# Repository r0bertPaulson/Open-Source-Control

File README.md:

# Open-Source-Control
Collection of Open Source IoT Designs

-Unitary Controller Version 3.0 - This device will be suitable for control of automated and networked building equipment at the unitary level. For example, you could control a single airconditioner unit with this device.

Project Status:
1.	Use Version 3.0 - Full BOM and Academic Free License statement to be posted here shortly.

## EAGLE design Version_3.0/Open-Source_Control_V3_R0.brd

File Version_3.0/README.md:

New Modular Board which allows the creation of a family of devices to cover most Building Automation control use cases. 

This board will have headers that can connect to an add-on sub-board and other devices that are application specific.

For example, by adding an airflow sensor and two analog actuator outputs, you will have a device that can control a VAV (Variable Air Volume) terminal unit specifically.

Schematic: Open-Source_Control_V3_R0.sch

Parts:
C1, C2: DNI; C0603
C3, C6, C9, C10, C14, C15, C22, C79, C104, C301, C801, C802, C901: 0.1uF, 6.3V; C0402
C4: 47uF; C0805
C8: 1nF; C0402
C11: 220uF, 6.3V, T491C227K006AT; C/6032-28R
C21: 10uF, 10V; C0805
C85, C87, C88: 2200pF, 6.3V; C0402
C100: 1000uF, 50V, UHE1H102MHD6; PCAP_16X25-THRU-ELECT
C101, C102, C105: 0.47uF, 100V, X7R; 1206
C106: 0.1uF, 50V; 1206
C111, C121, C131, C141, C151, C161: 1uF; C0805
C401, C402, C403: 0.1uF, 16V; C0402
C404, C405: 10uF, 16V; C0805
C406: 4.7uF, 16V, T491A475K016AT; A/3216-18R
C803: 4.7uF, 6.3V; C0402
D1, D4, D5, D6, D7, D19, D31, D32, D33, D34, D302, D402, D802: LTST-C191KGKT; EIA-STD
D3: S1D; SMA
D18: B550C-13-F; SMC
D301, D401, D801: LTST-C191KRKT; EIA-STD
D305, D405: SM712; SOT23-3
D403, D404: MBR0520LT; SOD123
D805: CDSOT23-T24CAN; SOT23-3
EC30, EC31, EC34: 0.1uF, 6.3V; C0402
EC32: 10uF, 10V; C0805
EC33: 1uF, 10V; C0402
EC35: 470pF, 6.3V; C0402
EC36, EC37, EC38, EC39: 15pF, DNI; C0402
EC40: 0.022uF, 10V; C0402
EC41, EC42: 30pF, 50V; C0402
ER98, ER99, ER100, ER105: 1.5K, 1%; R0402
ER101, ER102, ER103, ER104, ER120, ER129: 10K, 1%; R0402
ER106, ER107, ER108, ER109: 49.9, 1%; R0402
ER110, ER111, ER112, ER113, ER114, ER116, ER118, ER119, ER123, ER124: 100, 1%; R0402
ER115, ER117: 470, 1%; R0402
ER122, ER126: 0, 1%; R0402
ER125: 1M, 1%, DNI; R0402
ER127: 10, 1%; R0402
ER128: 12.1K, 1%; R0402
F1: 60V, 750mA, R075; PTH
F401, F402: TBU-CA085-300-WH; TBU-CA
FB7: 150ohm, 800mA; C0805
FUD1, FUD2, FUD3, FUD4, FUD5, FUD6: FIDUCIAL; FIDUCIAL_40MIL
G1: CR2032V
GDT1: 2036-07-B3; 2036-XX-B3
IC2: ULN2003AD; SO16
IC4, IC5: 74HC165D; SO16
IC10, IC11, IC12, IC14: MCP6002SMT; SOIC8
J1, J3, J7, J11, J12, J13, J21, J22, J23, J31, J32, J33, J41, J42, J43, J45, J51, J52, J53, J61, J62, J63, J450, J454: 826646-2; H2-2.54
J24: 6p-2.54; H3-2.54
K1, K2, K3, K4: G5LE-14-CF DC24; JS-M
L2: SRP1265A-470M; SRP1265
MTG1, MTG2, MTG3, MTG4: MOUNT-PAD-ROUND3.6; 3,6-PAD
Q1: MMBT2907; SOT23-BEC
R3, R4, R25, R28, R29, R30, R33: 0, 1%; R0402
R5, R11: 0; R0402
R6, R163: 100K, DNI; R0402
R8, R301, R302, R401, R402, R801, R802: 1K; R0402
R10: 0, 1%; R0805
R12, R13, R26, R164: 1.5K, 1%; R0402
R15: 40.2K; R0402
R18, R22, R39, R40, R41: 4.75K, 1%; R0402
R20, R168, R171, R172, R173, R174: 10K; R0402
R21: 499; R0402
R27, R53, R55, R56, R57, R58, R59, R60, R61, R62, R63, R67, R68, R71, R81, R82, R83: 100K, 1%; R0402
R31: 22, 1%; R0402
R34: .1, 0805; R0805
R35: 1K; RN0804
R54, R64, R65, R66, R70, R72, R73, R74, R75, R76, R77, R78, R79, R80, R84, R85: 100K, 1%, DNI; R0402
R69: 100, 1%; R0402
R86, R87, R88, R89, R90, R91, R92, R169, R170: 10K, 1%; R0402
R181, R182, R183, R184, R185, R186: B72520T0300K062; CT/CN1206
R211, R221, R231, R241, R251, R261: 80, 0.1%; 0309/12
R212, R214, R222, R224, R232, R234, R242, R244, R252, R254, R262, R264: 10K, 1%; R0805
R213, R223, R233, R243, R253, R263: 2K, 1%; R0805
R215, R225, R235, R245, R255, R265: 100K; R0805
R281, R282, R291: 10K; RN0804
R303, R304: 1K, DNI; R0402
R305: 150, 1%; R0805
R901, R902: 1.5K, 1% DNI; R0402
RTC1: DS3231MZ+; SO08
S1, S2: KMR231GLFS; SW4SMD_63X161LS
S11, S12: P101
S13: DS04; DS-04
T4: DA2304-AL; DA230X-AL
TP1, TP2, TP3, TP4, TP11, TP12, TP13, TP14, TP15, TP16, TP21, TP22, TP23, TP24, TP26, TP31, TP32, TP33: TPB0,65; TP_B0,65
TP5, TP6, TP7, TP8, TP9, TP10, TP17, TP18, TP19, TP20: TESTPAD/W_HOLE_1X1
U1: OSD3358-512M-ICB; OSD335X-BGA-400
U2: TPD4S012_DRY_6_P1_M; DRY6
U4: APX811-31UGSOT; SOT143-R
U5: TLVH431; SOT23-3
U6: SN74LVC2G241_DCU_8; DCU8
U16: AT97SC3205T-G3M4400B; QFN32-0.4-4X4MM
U27: LAN8710; LAN8710A-QFN32
U28: TCAN1051HV; BEAGLEBONE_BLUE_D8
U29: MAX3483EESA+T; 21-0041B_8
U40: ISO3086TDW; DW16
VREG1: LM2596S-5.0; TO263-5
VREG2: L7824CV; 78XXL
VREG4: TPS76350; DBV5
X1: 10118194-0001LF; 10118194-0001LF(MICRO-USB-B-AMPHENOL-FCI)
X2: J0011D01BNL
X3, X10, X11, X12, X31: MC4
X4: CTI-JTAG
X5: DM3CS-SF
X6: 6p-2.54; H6-2.54
X7, X8: TH-2X10; H2X10-2.54
X9: 5600200420
X21: MC12
X24: MSTBA2
X41: MSTBA3
Y7: ECS-250-12-30-GN-TR; XTAL_2-SMD(5X3.2MM)

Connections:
1P8V_REF_1: IC10.8 (V+), IC11.8 (V+), IC14.1 (OUT), IC14.2 (-IN), R212.2, R222.2, R232.2, R242.2
1P8V_REF_2: IC12.8 (V+), IC14.6 (-IN), IC14.7 (OUT), R252.2, R262.2
5V_OUT: D18.C, L2.1, VREG1.2 (OUT)
24LIN_IN: C105.1, J24.1, VREG2.IN
24VAC: D3.A, F1.P$2 (2)
24VAC_IN: F1.P$1 (1), X3.4, X24.1
24VDC_AUX: C106.1, D19.1 (A), D31.1 (A), D32.1 (A), D33.1 (A), D34.1 (A), IC2.9 (CD+), J24.3, K1.1, K2.1, K3.1, K4.1, VREG2.OUT, X8.11, X8.19, X31.4
24VDC_UNREG: C100.1, C101.1, D3.C, J24.2, VREG1.1 (IN)
41_A: F402.1, GDT1.1, X41.2
41_B: F401.1, GDT1.2, X41.1
485_A: D305.1, R304.2, R305.2, U29.6 (A), X3.2
485_B: D305.2, R303.1, R305.1, U29.7 (B), X3.3
485_RXD: D402.2 (C), J45.1, U40.5 (R)
485_TXD: D401.2 (C), J45.2, U40.8 (D)
AGND: C8.2, C9.2, C10.2, C111.2, C121.2, C131.2, C141.2, C151.2, C161.2, IC10.4 (V-), IC11.4 (V-), IC12.4 (V-), J7.1, R25.2, R181.2, R182.2, R183.2, R184.2, R185.2, R186.2, R211.1, R213.2, R215.2, R221.1, R223.2, R225.2, R231.1, R233.2, R235.2, R241.1, R243.2, R245.2, R251.1, R253.2, R255.2, R261.1, R263.2, R265.2, U1.Y9 (AGND_ADC), X10.2, X10.4, X11.2, X11.4, X12.2, X12.4
AIN0: U1.Y10 (AIN0)
AIN1: IC10.1 (OUT), IC10.2 (-IN), R215.1, U1.W10 (AIN1)
AIN2: IC10.6 (-IN), IC10.7 (OUT), R225.1, U1.V10 (AIN2)
AIN3: IC11.1 (OUT), IC11.2 (-IN), R235.1, U1.V9 (AIN3)
AIN4: IC11.6 (-IN), IC11.7 (OUT), R245.1, U1.Y11 (AIN4)
AIN5: IC12.1 (OUT), IC12.2 (-IN), R255.1, U1.W11 (AIN5)
AIN6: IC12.6 (-IN), IC12.7 (OUT), R265.1, U1.V11 (AIN6)
AIN7: U1.U12 (PMIC_MUX_OUT), U1.V12 (AIN7)
B03_NO: K3.NO (S), X21.6
BAT_SENSE: TP6.P$1, U1.E19 (PMIC_BAT_SENSE)
BO1: K1.2, R171.2, X8.10
BO1_AUTO: IC2.16 (O1), X8.9
BO1_C: K1.C, X21.11
BO1_NC: K1.NC (O), X21.10
BO1_NO: K1.NO (S), X21.12
BO2: K2.2, R172.2, X8.8
BO2_AUTO: IC2.15 (O2), X8.7
BO2_C: K2.C, X21.8
BO2_NC: K2.NC (O), X21.7
BO2_NO: K2.NO (S), X21.9
BO3: K3.2, R173.2, X8.6
BO3_AUTO: IC2.14 (O3), X8.5
BO3_C: K3.C, X21.5
BO3_NC: K3.NC (O), X21.4
BO4: K4.2, R174.2, X8.4
BO4_AUTO: IC2.13 (O4), X8.3
BO4_C: K4.C, X21.2
BO4_NC: K4.NC (O), X21.1
BO4_NO: K4.NO (S), X21.3
BO5_AUTO: IC2.12 (O5), X8.1
BO6_AUTO: IC2.11 (O6), X8.12
B_UART0_RX: R27.2, U6.2 (1A), X6.4
B_UART0_TX: U6.3 (2Y), X6.5
CAN1_RXD: D802.2 (C), U1.W7 (UART1_TXD), U28.4 (RXD)
CAN1_TXD: D801.2 (C), U1.Y7 (UART1_RXD), U28.1 (TXD)
CAN_H: D805.2, U28.7 (CANH), X31.3
CAN_L: D805.1, U28.6 (CANL), X31.2
CGND: MTG1.B3,6, MTG2.B3,6, MTG3.B3,6, MTG4.B3,6, R34.2, X1.CGND1 (SGND1), X1.CGND2 (SGND2), X1.CGND3 (SGND3), X1.CGND4 (SGND4), X1.CGND5 (SGND5), X1.CGND6 (SGND6), X2.S1 (SHD1), X2.S2 (SHD2), X5.9 (GND_1), X5.10 (GND_2), X5.11 (GND_3), X5.13 (GND_4)
CLKOUT2: C2.2, R3.2, X4.18 (EMU3)
CRS: ER124.1, U27.14 (CRS)
EEPROM_WP: J1.1, U1.M2 (EEPROM_WP)
EHRPWM1A: U1.C13 (GPMC_A2), X8.15
EHRPWM1B: U1.A12 (GPMC_A3)
EHRPWM2A: U1.A17 (GPMC_AD8), X8.13
EHRPWM2B: U1.C16 (GPMC_AD9), X8.14
E_LED_GRN: U27.3 (LED1/REGOFF), X2.9 (GRNA)
E_LED_YEL: ER120.2, U27.2 (LED2/!INTSEL), X2.12 (YELA)
GND: C1.1, C2.1, C3.2, C4.2, C6.1, C11.-, C14.2, C15.2, C21.2, C22.2, C79.2, C85.2, C87.2, C88.2, C100.2, C101.2, C102.2, C104.2, C105.2, C106.2, C301.2, C401.2, C404.2, C801.2, C802.2, C803.2, C901.2, D18.A, D305.3, D805.3, EC30.2, EC31.2, EC32.2, EC33.2, EC34.2, EC35.2, EC36.2, EC37.2, EC38.2, EC39.2, EC40.2, EC41.2, EC42.2, ER101.2, ER102.2, ER103.2, ER104.2, ER115.1, ER117.1, ER120.1, ER128.1, ER129.2, G1.-, IC2.8 (GND), IC4.8 (GND), IC4.15 (INH), IC5.3 (E), IC5.4 (F), IC5.5 (G), IC5.6 (H), IC5.8 (GND), IC5.10 (SER), IC5.15 (INH), IC14.4 (V-), J1.2, J3.2, J7.2, R6.1, R18.1, R26.2, R27.1, R34.1, R35.1, R35.2, R35.3, R35.4, R39.1, R53.1, R54.1, R55.1, R56.1, R57.1, R58.1, R59.1, R60.1, R61.1, R62.1, R63.1, R64.1, R65.1, R66.1, R67.1, R68.1, R168.2, R281.1, R281.2, R281.3, R281.4, R282.1, R282.2, R282.3, R282.4, R291.1, R291.2, R291.3, R291.4, R304.1, RTC1.5 (GND), S1.2, S1.4, S2.1, S2.3, TP8.P$1, U1.A1 (DGND), U1.A20 (DGND), U1.D4 (DGND), U1.D5 (DGND), U1.D15 (DGND), U1.D16 (DGND), U1.D17 (DGND), U1.E4 (DGND), U1.E5 (DGND), U1.E6 (DGND), U1.E7 (DGND), U1.E8 (DGND), U1.E9 (DGND), U1.E10 (DGND), U1.E11 (DGND), U1.E12 (DGND), U1.E13 (DGND), U1.E14 (DGND), U1.E15 (DGND), U1.E16 (DGND), U1.E17 (DGND), U1.F5 (DGND), U1.F10 (DGND), U1.F11 (DGND), U1.F16 (DGND), U1.F17 (DGND), U1.G5 (DGND), U1.G16 (DGND), U1.H5 (DGND), U1.H16 (DGND), U1.J5 (DGND), U1.J9 (DGND), U1.J10 (DGND), U1.J11 (DGND), U1.J12 (DGND), U1.J13 (DGND), U1.J16 (DGND), U1.K5 (DGND), U1.K6 (DGND), U1.K7 (DGND), U1.K8 (DGND), U1.K9 (DGND), U1.K12 (DGND), U1.K15 (DGND), U1.K16 (DGND), U1.L5 (DGND), U1.L6 (DGND), U1.L15 (DGND), U1.L16 (DGND), U1.M5 (DGND), U1.M15 (DGND), U1.M16 (DGND), U1.N5 (DGND), U1.N6 (DGND), U1.N15 (DGND), U1.N16 (DGND), U1.P5 (DGND), U1.P6 (DGND), U1.P7 (DGND), U1.P8 (DGND), U1.P9 (DGND), U1.P12 (DGND), U1.P13 (DGND), U1.P14 (DGND), U1.P15 (DGND), U1.P16 (DGND), U1.R5 (DGND), U1.R9 (DGND), U1.R10 (DGND), U1.R11 (DGND), U1.R12 (DGND), U1.R16 (DGND), U1.T4 (DGND), U1.T5 (DGND), U1.T6 (DGND), U1.T7 (DGND), U1.T8 (DGND), U1.T9 (DGND), U1.T10 (DGND), U1.T11 (DGND), U1.T12 (DGND), U1.T13 (DGND), U1.T14 (DGND), U1.T15 (DGND), U1.T16 (DGND), U1.T17 (DGND), U1.U4 (DGND), U1.U5 (DGND), U1.U15 (RTC_KALDO_ENN), U1.U16 (DGND), U1.U17 (DGND), U1.W13 (OSC1_GND), U1.Y1 (DGND), U1.Y20 (DGND), U2.4 (GND), U4.1 (GND), U6.1 (*1OE), U6.4 (GND), U16.2 (GND), U16.5 (TESTL), U16.6 (XTAMPER), U16.9 (GND), U16.18 (PIRQ#), U16.19 (ATEST), U16.20 (TWI_WAKEUP#), U16.21 (ATEST), U16.23 (GND), U16.24 (ATEST), U16.32 (GND), U27.33 (GND_EP), U28.2 (GND), U29.5 (GND), U40.3 (GND1), VREG1.3 (GND), VREG1.5 (EN), VREG1.6 (GND), VREG2.GND, X1.GND, X2.8 (D_GND), X3.1, X4.4 (TDIS), X4.8 (GND1), X4.10 (GND2), X4.12 (GND3), X4.16 (GND4), X4.20 (GND5), X5.6 (VSS), X6.1, X8.2, X8.16, X9.P$2 (2), X24.2, X31.1
GPIO0_7: U1.V15 (ECAP0_IN_PWM0_OUT), U29.2 (!RE), U29.3 (DE)
GPIO0_18: U1.K3 (USB0_DRVVBUS)
GPIO1_12: IC2.2 (I2), U1.C15 (GPMC_AD12)
GPIO1_13: IC2.3 (I3), U1.B15 (GPMC_AD13)
GPIO1_14: IC2.4 (I4), U1.A15 (GPMC_AD14)
GPIO1_15: IC2.5 (I5), U1.C14 (GPMC_AD15)
GPIO1_16: IC2.6 (I6), U1.A13 (GPMC_A0)
GPIO1_17: IC2.1 (I1), U1.B13 (GPMC_A1)
GPIO1_28: U1.C9 (GPMC_BEN1)
I2C0_SCL: R12.1, TP18.P$1, U1.U8 (PMIC_SCL), U1.V8 (I2C0_SCL), U16.29 (SM_CLK)
I2C0_SDA: R13.1, TP17.P$1, U1.U7 (PMIC_SDA), U1.V7 (I2C0_SDA), U16.30 (SM_DAT)
I2C2_SCL: R169.1, R901.1, RTC1.8 (SCL), TP20.P$1, U1.Y8 (UART1_RTSN), X9.P$4 (4)
I2C2_SDA: R170.1, R902.1, RTC1.7 (SDA), TP19.P$1, U1.W8 (UART1_CTSN), X9.P$1 (1)
ISO_485_A: D405.2, F402.3, U40.11 (Y), U40.14 (A)
ISO_485_B: D405.1, F401.3, U40.12 (Z), U40.13 (B)
ISO_GND: C402.2, C403.2, C405.2, C406.-, D405.3, GDT1.3, T4.P$6 (6), T4.P$7 (7), U40.9 (GND2_2), U40.15 (GND2), VREG4.2 (GND), X41.3
ISO_VCC: C402.1, C406.+, U40.16 (VCC2), VREG4.5 (VOUT)
ISO_VIN: C403.1, C405.1, D403.C, D404.C, VREG4.1 (VIN), VREG4.3 (ON/!OFF)
JTAG_EMU0: R40.1, U1.V18 (EMU0), X4.13 (EMU0)
JTAG_EMU1: R41.1, U1.V19 (EMU1), X4.14 (EMU1)
JTAG_TCK: U1.Y19 (TCK), X4.9 (TCKRTN), X4.11 (TCK)
JTAG_TDI: U1.Y18 (TDI), X4.3 (TDI)
JTAG_TDO: U1.W18 (TDO), X4.7 (TDO)
JTAG_TMS: U1.W19 (TMS), X4.1 (TMS)
JTAG_TRSTN: R39.2, U1.W20 (TRSTN), X4.2 (TRSTN)
LCD_DATA0: R68.2, R85.1, U1.T18 (LCD_DATA0), X7.19
LCD_DATA1: R67.2, R84.1, U1.T19 (LCD_DATA1), X7.20
LCD_DATA2: R66.2, R69.1, R83.1, U1.T20 (LCD_DATA2), X7.17
LCD_DATA3: R65.2, R82.1, U1.R18 (LCD_DATA3), X7.18
LCD_DATA4: R64.2, R81.1, U1.R19 (LCD_DATA4), X7.15
LCD_DATA5: R63.2, R80.1, U1.R20 (LCD_DATA5), X7.16
LCD_DATA6: R62.2, R79.1, U1.P18 (LCD_DATA6), X7.13
LCD_DATA7: R61.2, R78.1, U1.P19 (LCD_DATA7), X7.14
LCD_DATA8: R60.2, R77.1, U1.P20 (LCD_DATA8), X7.11
LCD_DATA9: R59.2, R76.1, U1.N18 (LCD_DATA9), X7.12
LCD_DATA10: R58.2, R75.1, U1.N19 (LCD_DATA10), X7.10
LCD_DATA11: R57.2, R74.1, U1.N20 (LCD_DATA11), X7.8
LCD_DATA12: R56.2, R73.1, U1.M18 (LCD_DATA12), X7.9
LCD_DATA13: R55.2, R72.1, U1.M19 (LCD_DATA13), X7.7
LCD_DATA14: R54.2, R71.1, U1.M20 (LCD_DATA14), X7.5
LCD_DATA15: R53.2, R70.1, U1.L18 (LCD_DATA15), X7.6
LCD_DE: R28.2, X7.4
LCD_HSYNC: R29.2, X7.3
LCD_PCLK: R31.2, X7.2
LCD_VSYNC: R30.2, X7.1
LDO_PGOOD: TP22.TP, U1.D13 (RTC_PWRONRSTN), U1.D14 (PMIC_LDO_PGOOD)
MDIO_CLK: U1.W1 (MDC), U27.17 (MDC)
MDIO_DATA: ER105.2, U1.V1 (MDIO), U27.16 (MDIO)
MII1_COL: ER123.2, U1.R2 (MII1_COL)
MII1_CRS: ER124.2, U1.R3 (MII1_CRS)
MII1_RXCLK: ER116.2, U1.T1 (MII1_RX_CLK)
MII1_RXD0: ER113.2, U1.T3 (MII1_RXD0)
MII1_RXD1: ER112.2, U1.U1 (MII1_RXD1)
MII1_RXD2: ER111.2, U1.U2 (MII1_RXD2)
MII1_RXD3: ER110.2, U1.U3 (MII1_RXD3)
MII1_RXDV: ER114.2, U1.R1 (MII1_RX_DV)
MII1_RXERR: ER118.2, U1.T2 (MII1_RX_ER)
MII1_TXCLK: ER119.2, U1.N1 (MII1_TX_CLK)
MII1_TXD0: U1.N2 (MII1_TXD0), U27.22 (TXD0)
MII1_TXD1: U1.N3 (MII1_TXD1), U27.23 (TXD1)
MII1_TXD2: U1.P1 (MII1_TXD2), U27.24 (TXD2)
MII1_TXD3: U1.P2 (MII1_TXD3), U27.25 (TXD3)
MII1_TXEN: U1.P3 (MII1_TX_EN), U27.21 (TXEN)
MMC0_CD: R92.1, U1.V4 (SPI0_CS1), X4.19 (EMU4), X5.12 (CARD_DETECTION_SWITCH)
MMC0_CLK: R88.1, U1.W3 (MMC0_CLK), X5.5 (CLK)
MMC0_CMD: R87.1, U1.W2 (MMC0_CMD), X5.3 (CMD)
MMC0_DAT0: R89.1, U1.Y3 (MMC0_DAT0), X5.7 (DAT0)
MMC0_DAT1: R90.1, U1.V3 (MMC0_DAT1), X5.8 (DAT1)
MMC0_DAT2: R86.1, U1.V2 (MMC0_DAT2), X5.1 (DAT2)
MMC0_DAT3: R91.1, U1.Y2 (MMC0_DAT3), X5.2 (CD/DAT3)
MODE2: ER99.2, ER123.1, U27.15 (COL/CRS_DV/MODE2)
unnamed: R10.1, X1.VBUS
unnamed: D7.2 (C), R35.8
unnamed: D31.2 (C), R171.1
unnamed: D802.1 (A), R802.2
unnamed: D801.1 (A), R801.2
unnamed: J51.1, J52.1, R185.1, R254.1, X12.1
unnamed: D1.2 (C), R26.1
unnamed: TP33.TP, U1.F18 (SYS_VDD1_CTL)
unnamed: ER117.2, X2.10 (GRNC)
unnamed: D6.2 (C), R35.7
unnamed: D5.2 (C), R35.6
unnamed: J11.1, J12.1, R181.1, R214.1, X10.1
unnamed: D4.2 (C), R35.5
unnamed: D402.1 (A), R402.2
unnamed: D401.1 (A), R401.2
unnamed: D301.1 (A), R301.2
unnamed: D302.1 (A), R302.2
unnamed: C151.1, IC12.3 (+IN), J53.1, R254.2
unnamed: J51.2, R251.2
unnamed: J53.2, R253.1
unnamed: J52.2, R252.1
unnamed: J61.1, J62.1, R186.1, R264.1, X12.3
unnamed: C161.1, IC12.5 (+IN), J63.1, R264.2
unnamed: J61.2, R261.2
unnamed: J11.2, R211.2
unnamed: J12.2, R212.1
unnamed: J63.2, R263.1
unnamed: J62.2, R262.1
unnamed: J13.2, R213.1
unnamed: J21.1, J22.1, R182.1, R224.1, X10.3
unnamed: C121.1, IC10.5 (+IN), J23.1, R224.2
unnamed: C111.1, IC10.3 (+IN), J13.1, R214.2
unnamed: J21.2, R221.2
unnamed: J23.2, R223.1
unnamed: J22.2, R222.1
unnamed: J31.1, J32.1, R183.1, R234.1, X11.1
unnamed: C131.1, IC11.3 (+IN), J33.1, R234.2
unnamed: J31.2, R231.2
unnamed: J33.2, R233.1
unnamed: R31.1, U1.U20 (LCD_PCLK)
unnamed: J32.2, R232.1
unnamed: R30.1, U1.U18 (LCD_VSYNC)
unnamed: J41.1, J42.1, R184.1, R244.1, X11.3
unnamed: C141.1, IC11.5 (+IN), J43.1, R244.2
unnamed: J41.2, R241.2
unnamed: J43.2, R243.1
unnamed: J42.2, R242.1
unnamed: R29.1, U1.U19 (LCD_HSYNC)
unnamed: R28.1, U1.V20 (LCD_AC_BIAS_EN)
unnamed: D403.A, T4.P$8 (8)
unnamed: D404.A, T4.P$5 (5)
unnamed: T4.P$1 (1), U40.1 (D1)
unnamed: T4.P$4 (4), U40.2 (D2)
unnamed: D19.2 (C), R168.1
unnamed: EC40.1, ER122.2, X2.4 (TCT), X2.5 (RCT)
unnamed: IC4.6 (H), R282.5, S12.8
unnamed: IC4.5 (G), R282.6, S12.4
unnamed: IC4.4 (F), R282.7, S12.2
unnamed: IC4.3 (E), R282.8, S12.1
unnamed: IC4.14 (D), R281.5, S11.8
unnamed: IC4.13 (C), R281.6, S11.4
unnamed: IC4.12 (B), R281.7, S11.2
unnamed: IC4.11 (A), R281.8, S11.1
unnamed: IC4.10 (SER), IC5.9 (QH)
unnamed: IC5.11 (A), R291.8, S13.8
unnamed: IC5.12 (B), R291.7, S13.7
unnamed: IC5.13 (C), R291.6, S13.6
unnamed: IC5.14 (D), R291.5, S13.5
unnamed: G1.+, RTC1.6 (VBAT)
unnamed: J3.1, R69.2
unnamed: D32.2 (C), R172.1
unnamed: ER126.1, U27.5 (XTAL1/CLKIN)
unnamed: EC42.1, ER125.2, ER126.2, Y7.P$2 (2)
unnamed: EC41.1, ER127.2, Y7.P$1 (1)
unnamed: ER125.1, ER127.1, U27.4 (XTAL2)
unnamed: ER128.2, U27.32 (RBIAS)
unnamed: ER129.1, U27.18 (NINT/TXER/TXD4)
unnamed: D33.2 (C), R173.1
unnamed: D34.2 (C), R174.1
unnamed: EC33.1, EC35.1, U27.6 (VDDCR)
unnamed: ER115.2, X2.11 (YELC)
unnamed: R15.2, R20.1, U5.1 (REF)
unnamed: Q1.B, R21.1, U5.2 (CATHODE)
unnamed: R4.1, U1.W14 (XDMA_EVENT_INTR0)
unnamed: R11.1, S1.1, S1.3
unnamed: R8.2, U4.2 (RESET#)
unnamed: R5.2, R11.2, U4.3 (MR#)
unnamed: R3.1, U1.V14 (XDMA_EVENT_INTR1)
OSC1_IN: R164.2, RTC1.1 (32KHZ), U1.Y13 (OSC1_IN)
OSC1_OUT: U1.Y14 (OSC1_OUT)
OSC_CTL: TP32.TP, U1.M1 (OSC0_CTL)
PMIC_INT: TP24.TP, U1.J17 (PMIC_NINT), U1.K17 (EXTINTN)
PMIC_MUX_IN: R18.2, R22.1, U1.F19 (PMIC_MUX_IN)
PMIC_NRESET: U1.A19 (PMIC_NRESET), X8.18
PMIC_NWAKEUP: TP23.TP, U1.G17 (PMIC_NWAKEUP), U1.H17 (EXT_WAKEUP)
PMIC_PGOOD: TP26.TP, U1.D11 (PWRONRSTN), U1.D12 (PMIC_PGOOD)
PR1_PRU0_PRU_R30_6: U1.V17 (MCASP0_AXR1), U40.6 (!RE)
PR1_PRU0_PRU_R30_7: U1.V16 (MCASP0_AHCLKX), U40.7 (DE)
PR1_UART0_RXD: J450.1, U1.W4 (SPI0_D1)
PR1_UART0_TXD: J450.2, U1.Y4 (SPI0_CS0)
PWRONRSTN: R5.1, U1.C17 (PWRONRSTN_OD)
PWR_BUT: S2.2, S2.4, U1.A18 (PMIC_PB_IN)
PWR_EN: TP21.TP, U1.D9 (PMIC_POWER_EN), U1.D10 (PMIC_PWR_EN)
RTC_RST: R163.1, RTC1.4 (RST), U1.K20 (GPMC_CSN0)
RXD0: ER98.2, ER113.1, U27.11 (RXD0/MODE0)
RXD1: ER100.2, ER112.1, U27.10 (RXD1/MODE1)
RXD2: ER103.1, ER111.1, U27.9 (RXD2/RMIISEL)
RXD3: ER102.1, ER110.1, U27.8 (RXD3/PHYAD2)
RX_CLK: ER104.1, ER116.1, U27.7 (RXCLK/PHYAD1)
RX_DV: ER114.1, U27.26 (RXDV)
RX_ERR: ER101.1, ER118.1, U27.13 (RXER/RXD4/PHYAD0)
RX_N: EC37.1, ER107.2, U27.30 (RXN), X2.6 (RXN)
RX_P: EC36.1, ER106.2, U27.31 (RXP), X2.3 (RXP)
SPI1_CS0: IC4.1 (SH/!LD), IC5.1 (SH/!LD), U1.W17 (MCASP0_AHCLKR)
SPI1_D0: IC4.9 (QH), U1.Y16 (MCASP0_FSX)
SPI1_D1: U1.W16 (MCASP0_AXR0)
SPI1_SCLK: IC4.2 (CLK), IC5.2 (CLK), U1.Y17 (MCASP0_ACLKX)
SYS_ADC_1P8V: C10.1, IC14.3 (+IN), IC14.5 (+IN), R33.2, U1.Y12 (SYS_ADC_1P8V)
SYS_RESETN: C14.1, R6.2, R8.1, TP31.TP, U1.B17 (WARMRSTN), U16.17 (LRESET#), U27.19 (!RST), X4.15 (SRST)
SYS_RTC_1P8V: Q1.C, R15.1, TP14.TP, U1.K13 (SYS_RTC_1P8V), U1.K14 (SYS_RTC_1P8V), U1.L13 (SYS_RTC_1P8V), U1.L14 (SYS_RTC_1P8V), U1.M13 (VDDS_RTC), U1.M14 (VDDS), U5.3 (ANODE)
SYS_VDD1_3P3V: C6.2, C15.1, C21.1, C22.1, C79.1, C85.1, C87.1, C88.1, C104.1, C301.1, C401.1, C404.1, C802.1, C901.1, EC34.1, ER98.1, ER99.1, ER100.1, ER105.1, FB7.1, IC4.16 (VCC), IC5.16 (VCC), IC14.8 (V+), R12.2, R13.2, R22.2, R40.2, R41.2, R70.2, R71.2, R72.2, R73.2, R74.2, R75.2, R76.2, R77.2, R78.2, R79.2, R80.2, R81.2, R82.2, R83.2, R84.2, R85.2, R86.2, R87.2, R88.2, R89.2, R90.2, R91.2, R92.2, R163.2, R164.1, R169.2, R170.2, R301.1, R302.1, R303.2, R401.1, R402.1, R801.1, R802.1, R901.2, R902.2, RTC1.2 (VCC), S11.C, S12.C, S13.1, S13.2, S13.3, S13.4, T4.P$2 (2), T4.P$3 (3), TP12.TP, U1.F8 (EMMC_VCC), U1.F9 (EMMC_VCC), U1.G8 (EMMC_VCC), U1.G9 (EMMC_VCC), U1.H7 (EMMC_VCCQ), U1.H8 (EMMC_VCCQ), U1.H14 (SYS_VDD1_3P3V), U1.H15 (SYS_VDD1_3P3V), U1.J7 (EMMC_VCCQ), U1.J8 (EMMC_VCCQ), U1.J14 (SYS_VDD1_3P3V), U1.J15 (SYS_VDD1_3P3V), U4.4 (VCC), U6.7 (2OE), U6.8 (VCC), U16.1 (VCC), U16.8 (VCC), U16.22 (VCC), U27.12 (VDDIO), U28.5 (VIO), U29.8 (VCC), U40.4 (VCC1), X4.5 (TVDD), X5.4 (VDD), X9.P$3 (3)
SYS_VDD2_3P3V: D1.1 (A), TP13.TP, U1.F12 (SYS_VDD2_3P3V), U1.F13 (SYS_VDD2_3P3V), U1.G12 (SYS_VDD2_3P3V), U1.G13 (SYS_VDD2_3P3V)
SYS_VDD3_3P3V: Q1.E, R20.2, R21.2, TP16.TP, U1.K10 (SYS_VDD3_3P3V), U1.K11 (SYS_VDD3_3P3V), U1.L7 (SYS_VDD3_3P3V), U1.L8 (SYS_VDD3_3P3V), U1.L9 (SYS_VDD3_3P3V), U1.L10 (SYS_VDD3_3P3V), U1.L11 (SYS_VDD3_3P3V), U1.L12 (SYS_VDD3_3P3V), U1.M7 (VDDSHV4), U1.M8 (VDDSHV5), U1.M9 (VDDSHV3), U1.M10 (VDDSHV2), U1.M11 (VDDSHV1), U1.M12 (VDDSHV6)
SYS_VDD_1P8V: TP15.TP, U1.N7 (SYS_VDD_1P8V), U1.N8 (SYS_VDD_1P8V), U1.N9 (SYS_VDD_1P8V), U1.N10 (SYS_VDD_1P8V), U1.N11 (SYS_VDD_1P8V), U1.N12 (SYS_VDD_1P8V), U1.N13 (SYS_VDD_1P8V), U1.N14 (SYS_VDD_1P8V), U1.P10 (SYS_VDD_1P8V), U1.P11 (SYS_VDD_1P8V)
SYS_VOUT: C4.1, TP11.TP, U1.F14 (SYS_VOUT), U1.F15 (SYS_VOUT), U1.G14 (SYS_VOUT), U1.G15 (SYS_VOUT)
TEMP_SENSE: TP7.P$1, U1.E20 (PMIC_TS)
TPM_GPIO0: U1.W15 (MCASP0_FSR), U16.12 (GPIO)
TPM_GPIO1: TP9.P$1, U1.V6 (UART0_CTSN), U16.3 (GPIO-EXPRESS-00)
TPM_GPIO2: TP10.P$1, U1.V5 (UART0_RTSN), U16.4 (PP/GPIO)
TX_CLK: ER119.1, U27.20 (TXCLK)
TX_N: EC39.1, ER109.2, U27.28 (TXN), X2.2 (TXN)
TX_P: EC38.1, ER108.2, U27.29 (TXP), X2.1 (TXP)
UART0_RX: U1.Y6 (UART0_RXD), U6.6 (1Y)
UART0_TX: U1.W6 (UART0_TXD), U6.5 (2A)
UART2_RXD: D302.2 (C), U1.Y5 (SPI0_SCLK), U29.1 (RO)
UART2_TXD: D301.2 (C), U1.W5 (SPI0_D0), U29.4 (DI)
UART4_RXD: J454.1, U1.B9 (GPMC_WAIT0)
UART4_TXD: J454.2, U1.A9 (GPMC_WPN)
USB0_ID: U1.L1 (USB0_ID), U2.3 (ID), X1.ID
USB0_N: U1.K2 (USB0_DM), U2.1 (D-), X1.D-
USB0_P: U1.L2 (USB0_DP), U2.2 (D+), X1.D+
USR0: D7.1 (A), U1.C12 (GPMC_A5)
USR1: D6.1 (A), U1.A11 (GPMC_A6)
USR2: D5.1 (A), U1.B11 (GPMC_A7)
USR3: D4.1 (A), U1.C11 (GPMC_A8)
VDDS_DDR: TP2.TP, U1.U9 (VDDS_DDR)
VDDS_PLL: TP3.TP, U1.U10 (VDDS_PLL)
VDD_5V: C11.+, C102.1, C801.1, C803.1, L2.2, U1.C18 (VIN_AC), U1.C19 (VIN_AC), U1.C20 (VIN_AC), U28.3 (VCC), VREG1.4 (FB)
VDD_BAT: TP5.P$1, U1.D18 (VIN_BAT), U1.D19 (VIN_BAT), U1.D20 (VIN_BAT)
VDD_CORE: TP4.TP, U1.U13 (VDD_CORE)
VDD_ETH_PHY: EC30.1, EC31.1, EC32.1, ER106.1, ER107.1, ER108.1, ER109.1, ER122.1, FB7.2, U27.1 (VDD2A), U27.27 (VDD1A)
VDD_MPU: TP1.TP, U1.U6 (VDD_MPU)
VDD_USB_5V: C3.1, R10.2, U1.B18 (VIN_USB), U1.B19 (VIN_USB), U1.B20 (VIN_USB), U1.K1 (USB0_VBUS), U2.6 (VBUS)
VREFN: R25.1, U1.W9 (VREFN)
VREFP: C8.1, C9.1, R33.1, U1.W12 (VREFP)
XDMA_EVENT_INTR0: C1.2, R4.2, X4.17 (EMU2)

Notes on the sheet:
Power & Reset
Clocks, Analog & USB
SiP Interfaces
Boot configuration
10/100BASE-T Ethernet
LCD Header
Micro SD card slot
User LEDs
JTAG Header
USB Client
SiP GND & Misc
1/15
3/15
2/15
4/15
5/15
6/15
9/15
8/15
7/15
Mounting Holes
Fiducials
TPM
Local Network RS-485
Notes
12/15
11/15
10/15
13/15
14/15
Universal Inputs
Isolated RS-485 Interface
Power Supply
CAN Interface
User Config Switches
External Real Time Clk
Relay Outputs
Modular IO Connections
15/15

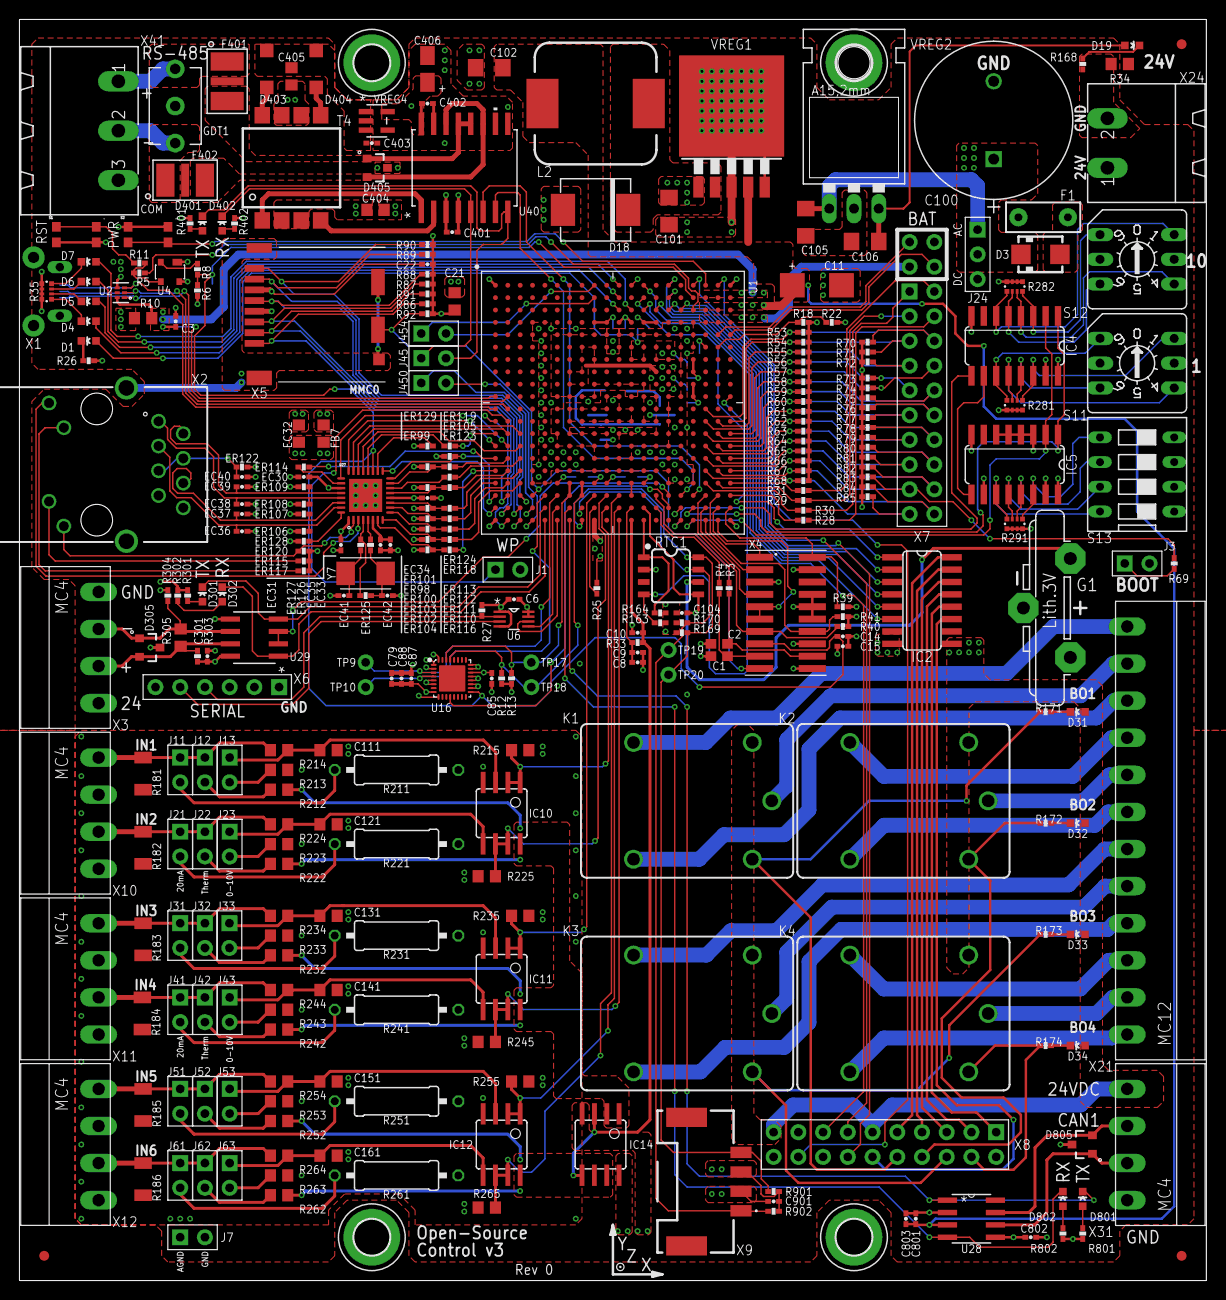
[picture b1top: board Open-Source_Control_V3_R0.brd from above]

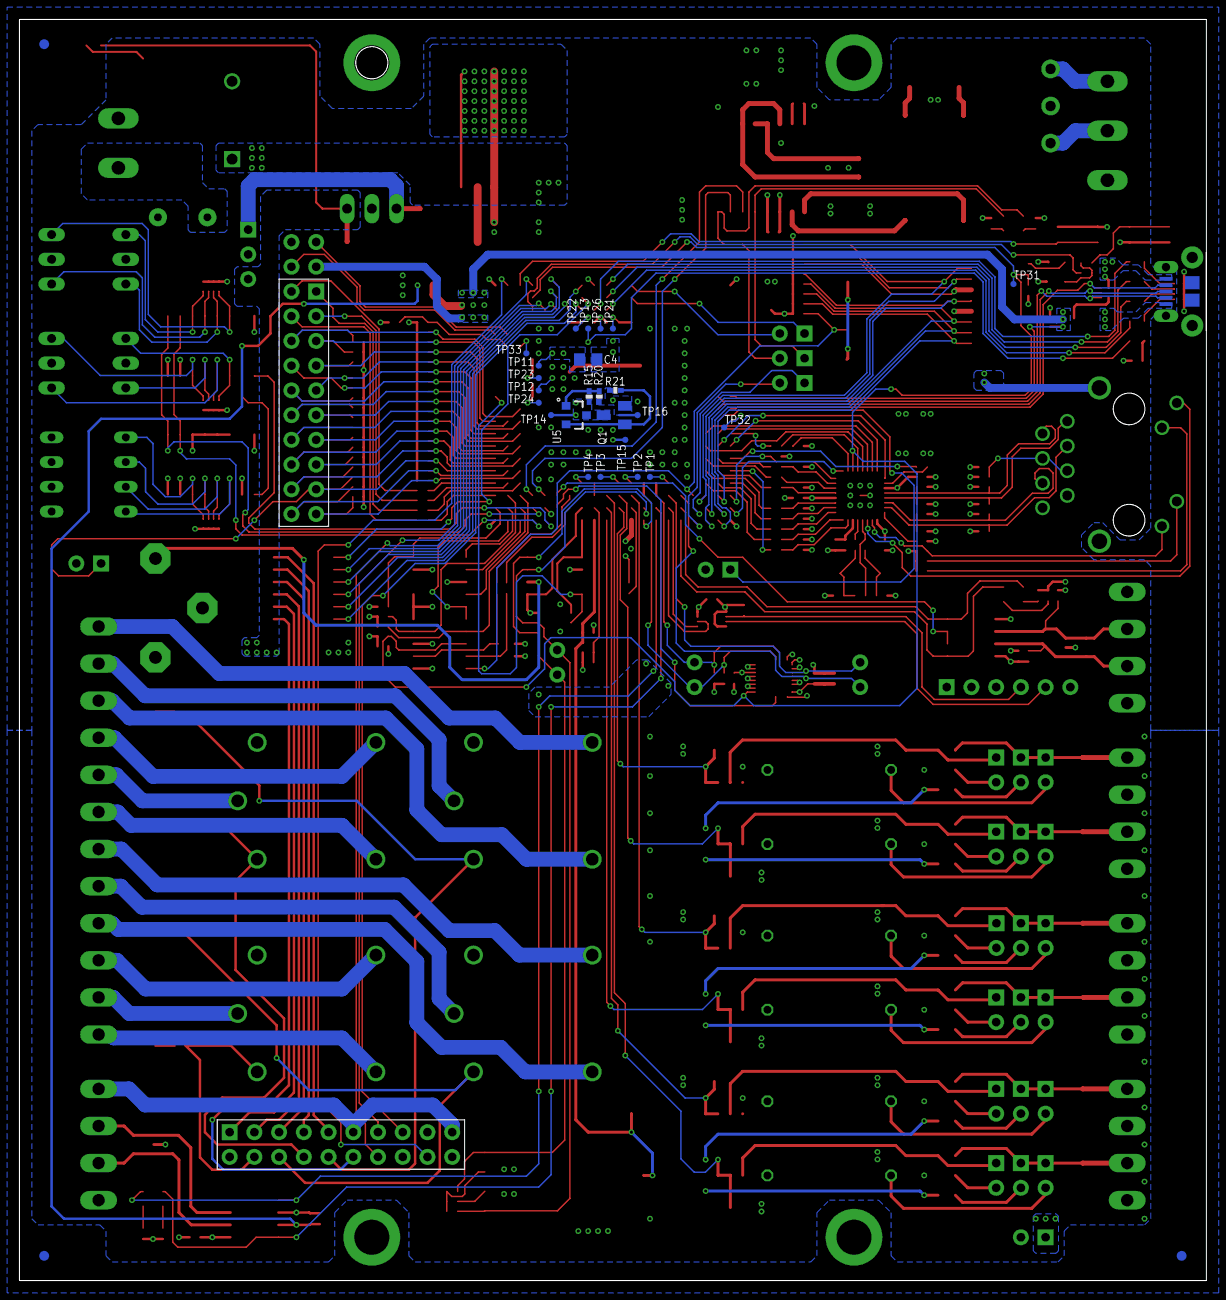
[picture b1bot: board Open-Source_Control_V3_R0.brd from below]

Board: 4 copper layers, 121.9 x 129.5 mm, 353 parts (28 on the bottom side), 284 nets.

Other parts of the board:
U$2: XYZ-LABEL

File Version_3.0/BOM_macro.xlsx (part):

Designator | Value | Footprint | Populate | MPN | Manufacturer | MPN | Manufacturer
C1 | DNI | C0603 | 0
C10 | 0.1uF, 6.3V | C0402 | 1 | GRM155R70J104KA01D | Murata
C100 | 1000uF, 50V, UHE1H102MHD6 | PCAP_16X25-THRU-ELECT | 0 | UHE1H102MHD6 | Nichicon
C101 | 0.47uF, 100V, X7R | 1206 | 1 | HMK316B7474KL-T | Taiyo Yuden
C102 | 0.47uF, 100V, X7R | 1206 | 1 | HMK316B7474KL-T | Taiyo Yuden
C104 | 0.1uF, 6.3V | C0402 | 1 | GRM155R70J104KA01D | Murata
C105 | 0.47uF, 100V, X7R | 1206 | 1 | HMK316B7474KL-T | Taiyo Yuden
C106 | 0.1uF, 50V | 1206 | 1 | C1206C104J5RACTU | KEMET
C11 | 220uF, 6.3V, T491C227K006AT | C/6032-28R | 1 | T491C227K006AT | KEMET
C111 | 1uF | C0805 | 1 | MF-CAP-0805-1uF | MacroFab
C121 | 1uF | C0805 | 1 | MF-CAP-0805-1uF | MacroFab
C131 | 1uF | C0805 | 1 | MF-CAP-0805-1uF | MacroFab
C14 | 0.1uF, 6.3V | C0402 | 1 | GRM155R70J104KA01D | Murata
C141 | 1uF | C0805 | 1 | MF-CAP-0805-1uF | MacroFab
C15 | 0.1uF, 6.3V | C0402 | 1 | GRM155R70J104KA01D | Murata
C151 | 1uF | C0805 | 1 | MF-CAP-0805-1uF | MacroFab
C161 | 1uF | C0805 | 1 | MF-CAP-0805-1uF | MacroFab
C2 | DNI | C0603 | 0
C21 | 10uF, 10V | C0805 | 1 | LMK212BJ106KG-T | Taiyo Yuden
C22 | 0.1uF, 6.3V | C0402 | 1 | GRM155R70J104KA01D | Murata
C3 | 0.1uF, 6.3V | C0402 | 1 | GRM155R70J104KA01D | Murata
C301 | 0.1uF, 6.3V | C0402 | 1 | GRM155R70J104KA01D | Murata
C4 | 47uF | C0805 | 1 | GRT21BR60J476ME13L | Murata
C401 | 0.1uF, 16V | C0402 | 1 | MF-CAP-0402-0.1uF | MacroFab
C402 | 0.1uF, 16V | C0402 | 1 | MF-CAP-0402-0.1uF | MacroFab
C403 | 0.1uF, 16V | C0402 | 1 | MF-CAP-0402-0.1uF | MacroFab
C404 | 10uF, 16V | C0805 | 1 | C0805C106K4PACTU | KEMET
C405 | 10uF, 16V | C0805 | 1 | C0805C106K4PACTU | KEMET
C406 | 4.7uF, 16V, T491A475K016AT | A/3216-18R | 1 | T491A475K016AT | KEMET
C6 | 0.1uF, 6.3V | C0402 | 1 | GRM155R70J104KA01D | Murata
C79 | 0.1uF, 6.3V | C0402 | 1 | GRM155R70J104KA01D | Murata
C8 | 1nF | C0402 | 1 | MF-CAP-0402-1nF | MacroFab
C801 | 0.1uF, 6.3V | C0402 | 1 | GRM155R70J104KA01D | Murata
C802 | 0.1uF, 6.3V | C0402 | 1 | GRM155R70J104KA01D | Murata
C803 | 4.7uF, 6.3V | C0402 | 1 | GRM155R60J475ME47D | Murata
C85 | 2200pF, 6.3V | C0402 | 1 | C0402C222K9RAC7867 | KEMET
C87 | 2200pF, 6.3V | C0402 | 1 | C0402C222K9RAC7867 | KEMET
C88 | 2200pF, 6.3V | C0402 | 1 | C0402C222K9RAC7867 | KEMET
C9 | 0.1uF, 6.3V | C0402 | 1 | GRM155R70J104KA01D | Murata
C901 | 0.1uF, 6.3V | C0402 | 1 | GRM155R70J104KA01D | Murata
D1 | LTST-C191KGKT | EIA-STD | 1 | LTST-C191KGKT | Lite-On
D18 | B550C-13-F | SMC | 1 | B550C-13-F | Diodes Inc.
D19 | LTST-C191KGKT | EIA-STD | 1 | LTST-C191KGKT | Lite-On
D3 | S1D | SMA | 1 | S1D | onsemi
D301 | LTST-C191KRKT | EIA-STD | 1 | LTST-C191KRKT | Lite-On
D302 | LTST-C191KGKT | EIA-STD | 1 | LTST-C191KGKT | Lite-On
D305 | SM712 | SOT23-3 | 1 | SM712-02HTG | Littelfuse
D31 | LTST-C191KGKT | EIA-STD | 1 | LTST-C191KGKT | Lite-On
D32 | LTST-C191KGKT | EIA-STD | 1 | LTST-C191KGKT | Lite-On
D33 | LTST-C191KGKT | EIA-STD | 1 | LTST-C191KGKT | Lite-On
D34 | LTST-C191KGKT | EIA-STD | 1 | LTST-C191KGKT | Lite-On
D4 | LTST-C191KGKT | EIA-STD | 1 | LTST-C191KGKT | Lite-On
D401 | LTST-C191KRKT | EIA-STD | 1 | LTST-C191KRKT | Lite-On
D402 | LTST-C191KGKT | EIA-STD | 1 | LTST-C191KGKT | Lite-On
D403 | MBR0520LT | SOD123 | 1 | MBR0520LT1G | onsemi
D404 | MBR0520LT | SOD123 | 1 | MBR0520LT1G | onsemi
D405 | SM712 | SOT23-3 | 1 | SM712-02HTG | Littelfuse
D5 | LTST-C191KGKT | EIA-STD | 1 | LTST-C191KGKT | Lite-On
D6 | LTST-C191KGKT | EIA-STD | 1 | LTST-C191KGKT | Lite-On
D7 | LTST-C191KGKT | EIA-STD | 1 | LTST-C191KGKT | Lite-On
D801 | LTST-C191KRKT | EIA-STD | 1 | LTST-C191KRKT | Lite-On
D802 | LTST-C191KGKT | EIA-STD | 1 | LTST-C191KGKT | Lite-On
D805 | CDSOT23-T24CAN | SOT23-3 | 1 | CDSOT23-T24CAN | Bourns
EC30 | 0.1uF, 6.3V | C0402 | 1 | GRM155R70J104KA01D | Murata
EC31 | 0.1uF, 6.3V | C0402 | 1 | GRM155R70J104KA01D | Murata
EC32 | 10uF, 10V | C0805 | 1 | LMK212BJ106KG-T | Taiyo Yuden
EC33 | 1uF, 10V | C0402 | 1 | C0402C105K8PACTU | KEMET
EC34 | 0.1uF, 6.3V | C0402 | 1 | GRM155R70J104KA01D | Murata
EC35 | 470pF, 6.3V | C0402 | 1 | C0402C471K9RACTU | KEMET
EC36 | 15pF, DNI | C0402 | 0
EC37 | 15pF, DNI | C0402 | 0
EC38 | 15pF, DNI | C0402 | 0
EC39 | 15pF, DNI | C0402 | 0
EC40 | 0.022uF, 10V | C0402 | 1 | C0402C223K8PACTU | KEMET
EC41 | 30pF, 50V | C0402 | 1 | GJM1555C1H300FB01D | Murata
EC42 | 30pF, 50V | C0402 | 1 | GJM1555C1H300FB01D | Murata
ER100 | 1.5K, 1% | R0402 | 1 | ERJPA2F1501X | Panasonic
ER101 | 10K, 1% | R0402 | 1 | RC0402FR-0710KL | Yageo
ER102 | 10K, 1% | R0402 | 1 | RC0402FR-0710KL | Yageo
ER103 | 10K, 1% | R0402 | 1 | RC0402FR-0710KL | Yageo
ER104 | 10K, 1% | R0402 | 1 | RC0402FR-0710KL | Yageo
ER105 | 1.5K, 1% | R0402 | 1 | ERJPA2F1501X | Panasonic
ER106 | 49.9, 1% | R0402 | 1 | RC0402FR-0749R9L | Yageo
ER107 | 49.9, 1% | R0402 | 1 | RC0402FR-0749R9L | Yageo
ER108 | 49.9, 1% | R0402 | 1 | RC0402FR-0749R9L | Yageo
ER109 | 49.9, 1% | R0402 | 1 | RC0402FR-0749R9L | Yageo
ER110 | 100, 1% | R0402 | 1 | RC0402FR-07100RL | Yageo
ER111 | 100, 1% | R0402 | 1 | RC0402FR-07100RL | Yageo
ER112 | 100, 1% | R0402 | 1 | RC0402FR-07100RL | Yageo
ER113 | 100, 1% | R0402 | 1 | RC0402FR-07100RL | Yageo
ER114 | 100, 1% | R0402 | 1 | RC0402FR-07100RL | Yageo
ER115 | 470, 1% | R0402 | 1 | RC0402FR-13470RL | Yageo
ER116 | 100, 1% | R0402 | 1 | RC0402FR-07100RL | Yageo
ER117 | 470, 1% | R0402 | 1 | RC0402FR-13470RL | Yageo
ER118 | 100, 1% | R0402 | 1 | RC0402FR-07100RL | Yageo
ER119 | 100, 1% | R0402 | 1 | RC0402FR-07100RL | Yageo
ER120 | 10K, 1% | R0402 | 1 | RC0402FR-0710KL | Yageo
ER122 | 0, 1% | R0402 | 1 | RC0402FR-070RL | Yageo
ER123 | 100, 1% | R0402 | 1 | RC0402FR-07100RL | Yageo
ER124 | 100, 1% | R0402 | 1 | RC0402FR-07100RL | Yageo
ER125 | 1M, 1%, DNI | R0402 | 0
ER126 | 0, 1% | R0402 | 1 | RC0402FR-070RL | Yageo
ER127 | 10, 1% | R0402 | 1 | RC0402FR-0710RL | Yageo
ER128 | 12.1K, 1% | R0402 | 1 | ERJ-2RKF1212X | Panasonic
ER129 | 10K, 1% | R0402 | 1 | RC0402FR-0710KL | Yageo
ER98 | 1.5K, 1% | R0402 | 1 | ERJPA2F1501X | Panasonic
ER99 | 1.5K, 1% | R0402 | 1 | ERJPA2F1501X | Panasonic
F1 | 60V, 750mA, R075 | PTH | 0 | MF-R075-99 | Bourns
F401 | TBU-CA085-300-WH | TBU-CA | 1 | TBU-CA085-300-WH | Bourns
F402 | TBU-CA085-300-WH | TBU-CA | 1 | TBU-CA085-300-WH | Bourns
FB7 | 150ohm, 800mA | C0805 | 1 | MU2029-151Y | Bourns
FUD1 | FIDUCIAL | FIDUCIAL_40MIL | 0
FUD2 | FIDUCIAL | FIDUCIAL_40MIL | 0
FUD3 | FIDUCIAL | FIDUCIAL_40MIL | 0
FUD4 | FIDUCIAL | FIDUCIAL_40MIL | 0
FUD5 | FIDUCIAL | FIDUCIAL_40MIL | 0
FUD6 | FIDUCIAL | FIDUCIAL_40MIL | 0
G1 | CR2032V | CR2032V | 0
GDT1 | 2036-07-B3 | 2036-XX-B3 | 0 | 2036-07-B3 | Bourns
IC10 | MCP6002SMT | SOIC8 | 1 | MCP6002T-E/SN | Microchip
IC11 | MCP6002SMT | SOIC8 | 1 | MCP6002T-E/SN | Microchip
IC12 | MCP6002SMT | SOIC8 | 1 | MCP6002T-E/SN | Microchip
IC14 | MCP6002SMT | SOIC8 | 1 | MCP6002T-E/SN | Microchip
IC2 | ULN2003AD | SO16 | 1 | ULN2003AD | Texas Instruments
IC4 | 74HC165D | SO16 | 1 | 74HC165D | Toshiba | SN74HC165DR | Texas Instruments
IC5 | 74HC165D | SO16 | 1 | 74HC165D | Toshiba | SN74HC165DR | Texas Instruments
J1 |  | H2-2.54 | 0
J11 |  | H2-2.54 | 0
J12 |  | H2-2.54 | 0
J13 |  | H2-2.54 | 0
J21 |  | H2-2.54 | 0
J22 |  | H2-2.54 | 0
J23 |  | H2-2.54 | 0
J24 | 6p-2.54 | H3-2.54 | 0 | P125-1106A1BS116A1 | YXCON
J3 |  | H2-2.54 | 0
J31 |  | H2-2.54 | 0
J32 |  | H2-2.54 | 0
J33 |  | H2-2.54 | 0
J41 |  | H2-2.54 | 0
J42 |  | H2-2.54 | 0
J43 |  | H2-2.54 | 0
J45 |  | H2-2.54 | 0
J450 |  | H2-2.54 | 0
J454 |  | H2-2.54 | 0
J51 |  | H2-2.54 | 0
J52 |  | H2-2.54 | 0
J53 |  | H2-2.54 | 0
J61 |  | H2-2.54 | 0
J62 |  | H2-2.54 | 0
J63 |  | H2-2.54 | 0
J7 |  | H2-2.54 | 0
K1 | G5LE-14-CF DC24 | JS-M | 0 | G5LE-14-CF DC24 | Omron
K2 | G5LE-14-CF DC24 | JS-M | 0 | G5LE-14-CF DC24 | Omron
K3 | G5LE-14-CF DC24 | JS-M | 0 | G5LE-14-CF DC24 | Omron
K4 | G5LE-14-CF DC24 | JS-M | 0 | G5LE-14-CF DC24 | Omron
L2 | SRP1265A-470M | SRP1265 | 1 | SRP1265A-470M | Bourns
MTG1 | MOUNT-PAD-ROUND3.6 | 3,6-PAD | 0
MTG2 | MOUNT-PAD-ROUND3.6 | 3,6-PAD | 0
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

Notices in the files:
OLD_Version_1.0/Open-Controller-Unitary_V1.sch:
(c) Copyright, Octavo Systems LLC, 2017
All Rights Reserved.
parts and their libraries:
SparkFun-Capacitors: Licensing: Creative Commons ShareAlike 4.0 International - https://creativecommons.org/licenses/by-sa/4.0
